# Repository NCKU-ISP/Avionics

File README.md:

# 國立成功大學 太空推進研究社
National Cheng Kung University Institute of Space Propulsion (NCKU ISP)

## Hardwares
### Stable
- ISP555
- ISP8266

### Beta
- ISP32

## Contributing
Contributions are what make the open source community such an amazing place to learn, inspire, and create. Any contributions you make are greatly appreciated.

If you have a suggestion that would make this better, please fork the repo and create a pull request. You can also simply open an issue with the tag "enhancement". Don't forget to give the project a star! Thanks again!

1. Fork the Project
2. Create your Feature Branch (git checkout -b feature/AmazingFeature)
3. Commit your Changes (git commit -m 'Add some AmazingFeature')
4. Push to the Branch (git push origin feature/AmazingFeature)
5. Open a Pull Request

## Contact
If you are interested in our project and want to support us, please contact us with the following:
- aerogroup2020@gmail.com
- [Facebook](https://www.facebook.com/ispncku)

## [LICENSE](https://github.com/NCKU-ISP/Avionics/blob/boards/LICENSE)
Distributed under the BSD 3-clause License. See LICENSE for more information.

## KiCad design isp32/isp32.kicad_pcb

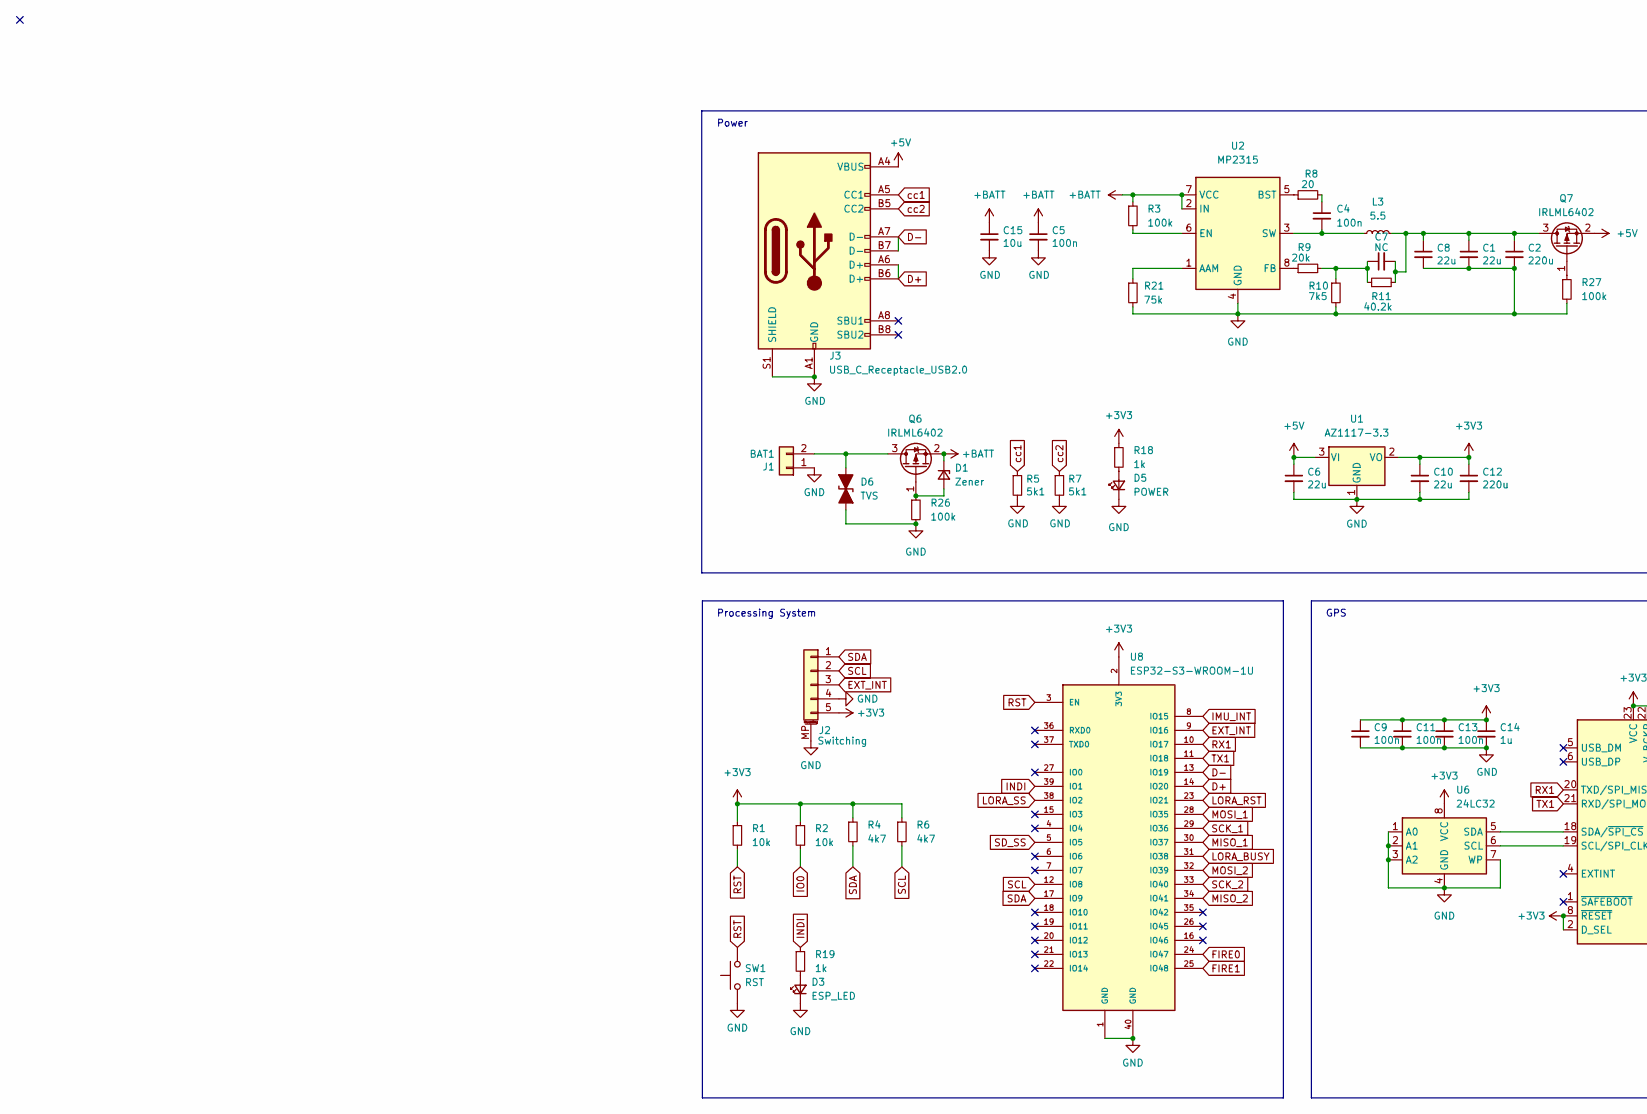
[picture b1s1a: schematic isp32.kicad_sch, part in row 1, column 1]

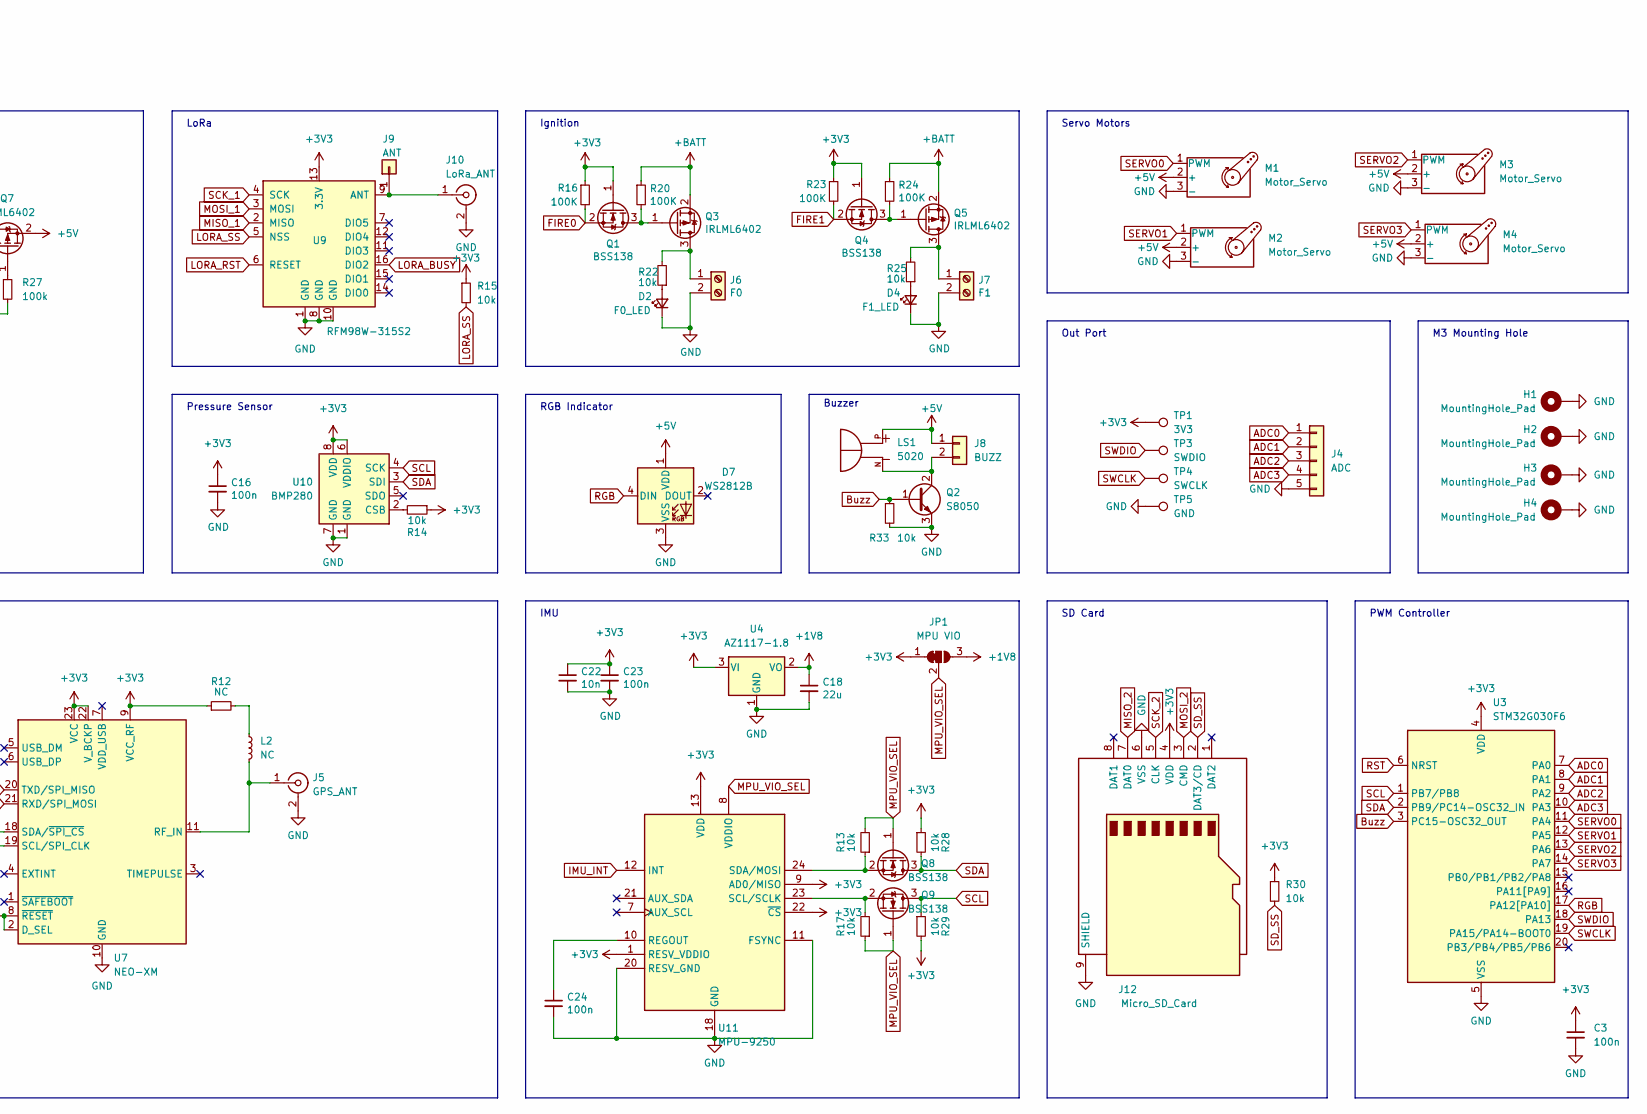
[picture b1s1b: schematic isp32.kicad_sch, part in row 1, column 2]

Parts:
C1, C6, C8, C10, C18: 22u; C_0603_1608Metric
C2, C12: 220u; CP_EIA-3528-12_Kemet-T
C3, C4, C9, C11, C13, C16, C23, C24: 100n; C_0603_1608Metric
C5: 100n; C_0805_2012Metric
C7: NC; C_0603_1608Metric
C14: 1u; C_0603_1608Metric
C15: 10u; C_0805_2012Metric
C22: 10n; C_0603_1608Metric
D1: Zener; D_SOD-123
D2: F0_LED; LED_0603_1608Metric
D3: ESP_LED; LED_0603_1608Metric
D4: F1_LED; LED_0603_1608Metric
D5: POWER; LED_0603_1608Metric
D6: TVS; D_SMB
D7: WS2812B; LED_WS2812B_PLCC4_5.0x5.0mm_P3.2mm
H1, H2, H3, H4: MountingHole_Pad; MountingHole_3.2mm_M3_ISO7380_Pad
J1: BAT1; AMASS_XT60-M_1x02_P7.20mm_Vertical
J2: Switching; Molex_PicoBlade_53261-0571_1x05-1MP_P1.25mm_Horizontal
J3: USB_C_Receptacle_USB2.0; USB_C_Receptacle_Palconn_UTC16-G
J4: ADC; PinHeader_1x05_P1.27mm_Vertical
J5: GPS_ANT; U.FL_Hirose_U.FL-R-SMT-1_Vertical
J6: F0; TerminalBlock_Phoenix_MPT-0,5-2-2.54_1x02_P2.54mm_Horizontal
J7: F1; TerminalBlock_Phoenix_MPT-0,5-2-2.54_1x02_P2.54mm_Horizontal
J8: BUZZ; PinHeader_1x02_P1.27mm_Vertical
J9: ANT; PinHeader_1x01_P2.00mm_Vertical
J10: LoRa_ANT; U.FL_Hirose_U.FL-R-SMT-1_Vertical
J12: Micro_SD_Card; microSD_HC_Molex_47219-2001
JP1: MPU VIO
L2: NC; L_0805_2012Metric
L3: 5.5; L_Sunlord_SWPA5020S
LS1: 5020; XDCR_KSSG33J12-3; PARTREV 1.4
M1, M2, M3, M4: Motor_Servo; PinHeader_1x03_P2.54mm_Vertical
Q1, Q4, Q8, Q9: BSS138; SOT-23
Q2: S8050; SOT-23
Q3, Q5, Q6, Q7: IRLML6402; SOT-23
R1, R2, R13, R14, R15, R17, R22, R25, R28, R29, R30, R33: 10k; R_0603_1608Metric
R3, R26, R27: 100k; R_0603_1608Metric
R4, R6: 4k7; R_0603_1608Metric
R5, R7: 5k1; R_0603_1608Metric
R8: 20; R_0603_1608Metric
R9: 20k; R_0603_1608Metric
R10: 7k5; R_0603_1608Metric
R11: 40.2k; R_0603_1608Metric
R12: NC; R_0603_1608Metric
R16, R20, R23, R24: 100K; R_0603_1608Metric
R18, R19: 1k; R_0603_1608Metric
R21: 75k; R_0603_1608Metric
SW1: RST; SW_SPST_FSMSM
TP1: 3V3; TestPoint_Pad_D1.0mm
TP3: SWDIO; TestPoint_Pad_D1.0mm
TP4: SWCLK; TestPoint_Pad_D1.0mm
TP5: GND; TestPoint_Pad_D1.0mm
U1: AZ1117-3.3; SOT-89-3
U2: MP2315; TSOT-23-8
U3: STM32G030F6; TSSOP-20_4.4x6.5mm_P0.65mm
U4: AZ1117-1.8; SOT-89-3
U6: 24LC32; SOIC-8_3.9x4.9mm_P1.27mm
U7: NEO-XM; ublox_NEO
U8: ESP32-S3-WROOM-1U; XCVR_ESP32-S3-WROOM-1U; PARTREV v0.6
U9: RFM98W-315S2; HOPERF_RFM9XW_SMD
U10: BMP280; Bosch_LGA-8_2x2.5mm_P0.65mm_ClockwisePinNumbering
U11: MPU-9250; InvenSense_QFN-24_3x3mm_P0.4mm

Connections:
+1V8: C18.1, JP1.3 (B), U4.2 (VO)
+3V3: C3.1, C9.1, C10.1, C11.1, C12.1, C13.1, C14.1, C16.1, C22.1, C23.1, J2.5, J12.4 (VDD), JP1.1 (A), Q1.1 (G), Q4.1 (G), R1.1, R2.1, R4.1, R6.1, R12.1, R14.1, R15.1, R16.1, R18.1, R23.1, R28.1, R29.2, R30.1, TP1.1, U1.2 (VO), U3.4 (VDD), U4.3 (VI), U6.8 (VCC), U7.2 (D_SEL), U7.8 (~RESET), U7.9 (VCC_RF), U7.22 (V_BCKP), U7.23 (VCC), U8.2 (3V3), U9.13 (3.3V), U10.6 (VDDIO), U10.8 (VDD), U11.1 (RESV_VDDIO), U11.9 (AD0/MISO), U11.13 (VDD), U11.22 (~CS)
+5V: C6.1, D7.1 (VDD), J3.A4 (VBUS), J3.A9 (VBUS), J3.B4 (VBUS), J3.B9 (VBUS), J8.1, LS1.P, M1.2 (+), M2.2 (+), M3.2 (+), M4.2 (+), Q7.2 (S), U1.3 (VI); also elsewhere on the board
+BATT: C5.1, C15.1, D1.1 (K), Q3.2 (S), Q5.2 (S), Q6.2 (S), R3.1, R20.1, R24.1, U2.2 (IN), U2.7 (VCC); also elsewhere on the board
ADC0: J4.1, U3.7 (PA0)
ADC1: J4.2, U3.8 (PA1)
ADC2: J4.3, U3.9 (PA2)
ADC3: J4.4, U3.10 (PA3)
Buzz: Q2.1 (B), R33.1, U3.3 (PC15-OSC32_OUT)
D+: J3.A6 (D+), J3.B6 (D+), U8.14 (IO20)
D-: J3.A7 (D-), J3.B7 (D-), U8.13 (IO19)
EXT_INT: J2.3, U8.9 (IO16)
FIRE0: Q1.2 (S), R16.2, U8.24 (IO47)
FIRE1: Q4.2 (S), R23.2, U8.25 (IO48)
GND: C1.2, C2.2, C3.2, C5.2, C6.2, C8.2, C9.2, C10.2, C11.2, C12.2, C13.2, C14.2, C15.2, C16.2, C18.2, C22.2, C23.2, C24.2, D2.1 (K), D3.1 (K), D4.1 (K), D5.1 (K), D6.1 (A1), D7.3 (VSS), H1.1, H2.1, H3.1, H4.1, J1.1, J2.4, J2.MP (MountPin), J3.A1 (GND), J3.A12 (GND), J3.B1 (GND), J3.B12 (GND), J3.S1 (SHIELD), J4.5, J5.2 (Ext), J6.2, J7.2, J10.2 (Ext), J12.6 (VSS), J12.9 (SHIELD), M1.3 (-), M2.3 (-), M3.3 (-), M4.3 (-), Q2.3 (E), R5.2, R7.2, R10.2, R21.2, R26.2, R27.2, R33.2, SW1.1, TP5.1, U1.1 (GND), U2.4 (GND), U3.5 (VSS), U4.1 (GND), U6.1 (A0), U6.2 (A1), U6.3 (A2), U6.4 (GND), U6.7 (WP), U7.10 (GND), U7.12 (GND), U7.13 (GND), U7.24 (GND), U8.1 (GND), U8.40 (GND), U8.41_1 (GND), U8.41_2 (GND), U8.41_3 (GND), U8.41_4 (GND), U8.41_5 (GND), U8.41_6 (GND), U8.41_7 (GND), U8.41_8 (GND), U8.41_9 (GND), U9.1 (GND), U9.8 (GND), U9.10 (GND), U10.1 (GND), U10.7 (GND), U11.11 (FSYNC), U11.18 (GND), U11.20 (RESV_GND); also elsewhere on the board
IMU_INT: U8.8 (IO15), U11.12 (INT)
INDI: R19.1, U8.39 (IO1)
IO0: R2.2, U8.27 (IO0)
LORA_BUSY: U8.31 (IO38), U9.16 (DIO2)
LORA_RST: U8.23 (IO21), U9.6 (RESET)
LORA_SS: R15.2, U8.38 (IO2), U9.5 (NSS)
MISO_1: U8.30 (IO37), U9.2 (MISO)
MISO_2: J12.7 (DAT0), U8.34 (IO41)
MOSI_1: U8.28 (IO35), U9.3 (MOSI)
MOSI_2: J12.3 (CMD), U8.32 (IO39)
MPU_VIO_SEL: JP1.2 (C), Q8.1 (G), Q9.1 (G), R13.2, R17.1, U11.8 (VDDIO)
unnamed 26: C1.1, C2.1, C7.2, C8.1, L3.2, Q7.3 (D), R11.2; also elsewhere on the board
unnamed: C4.1, R8.2
unnamed: C4.2, L3.1, U2.3 (SW)
unnamed: C7.1, R9.2, R10.1, R11.1
unnamed: C24.1, U11.10 (REGOUT)
unnamed: D1.2 (A), Q6.1 (G), R26.1
unnamed: D2.2 (A), R22.1
unnamed: D3.2 (A), R19.2
unnamed: D4.2 (A), R25.1
unnamed: D5.2 (A), R18.2
unnamed: D6.2 (A2), J1.2, Q6.3 (D)
unnamed: J5.1 (In), L2.2, U7.11 (RF_IN)
unnamed: J6.1, Q3.3 (D), R22.2
unnamed: J7.1, Q5.3 (D), R25.2
unnamed: J8.2, LS1.N, Q2.2 (C)
unnamed: J9.1, J10.1 (In), U9.9 (ANT)
unnamed: L2.1, R12.2
unnamed: Q1.3 (D), Q3.1 (G), R20.2
unnamed: Q4.3 (D), Q5.1 (G), R24.2
unnamed: Q7.1 (G), R27.1
unnamed: Q8.2 (S), R13.1, U11.24 (SDA/MOSI)
unnamed: Q9.2 (S), R17.2, U11.23 (SCL/SCLK)
unnamed: R3.2, U2.6 (EN)
unnamed: R8.1, U2.5 (BST)
unnamed: R9.1, U2.8 (FB)
unnamed: R14.2, U10.2 (CSB)
unnamed: R21.1, U2.1 (AAM)
unnamed: U6.5 (SDA), U7.18 (SDA/~SPI_CS)
unnamed: U6.6 (SCL), U7.19 (SCL/SPI_CLK)
RGB: D7.4 (DIN), U3.17 (PA12[PA10])
RST: R1.2, SW1.2, U3.6 (NRST), U8.3 (EN)
RX1: U7.20 (TXD/SPI_MISO), U8.10 (IO17)
SCK_1: U8.29 (IO36), U9.4 (SCK)
SCK_2: J12.5 (CLK), U8.33 (IO40)
SCL: J2.2, Q9.3 (D), R6.2, R29.1, U3.1 (PB7/PB8), U8.12 (IO8), U10.4 (SCK)
SDA: J2.1, Q8.3 (D), R4.2, R28.2, U3.2 (PB9/PC14-OSC32_IN), U8.17 (IO9), U10.3 (SDI)
SD_SS: J12.2 (DAT3/CD), R30.2, U8.5 (IO5)
SERVO0: M1.1 (PWM), U3.11 (PA4)
SERVO1: M2.1 (PWM), U3.12 (PA5)
SERVO2: M3.1 (PWM), U3.13 (PA6)
SERVO3: M4.1 (PWM), U3.14 (PA7)
SWCLK: TP4.1, U3.19 (PA15/PA14-BOOT0)
SWDIO: TP3.1, U3.18 (PA13)
TX1: U7.21 (RXD/SPI_MOSI), U8.11 (IO18)
cc1: J3.A5 (CC1), R5.1
cc2: J3.B5 (CC2), R7.1

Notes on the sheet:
IMU
PWM Controller
Ignition
M3 Mounting Hole
Servo Motors
RGB Indicator
Out Port
Buzzer
Processing System
Pressure Sensor
LoRa
GPS
SD Card
Power

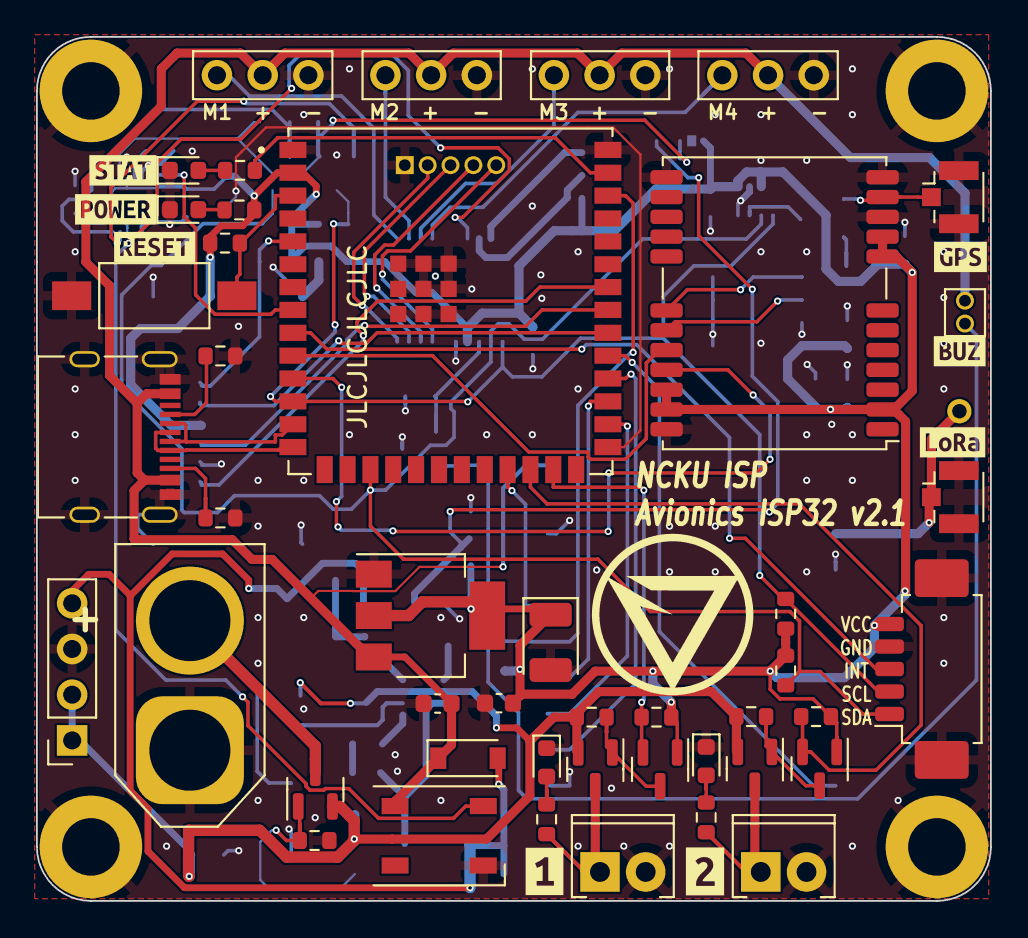
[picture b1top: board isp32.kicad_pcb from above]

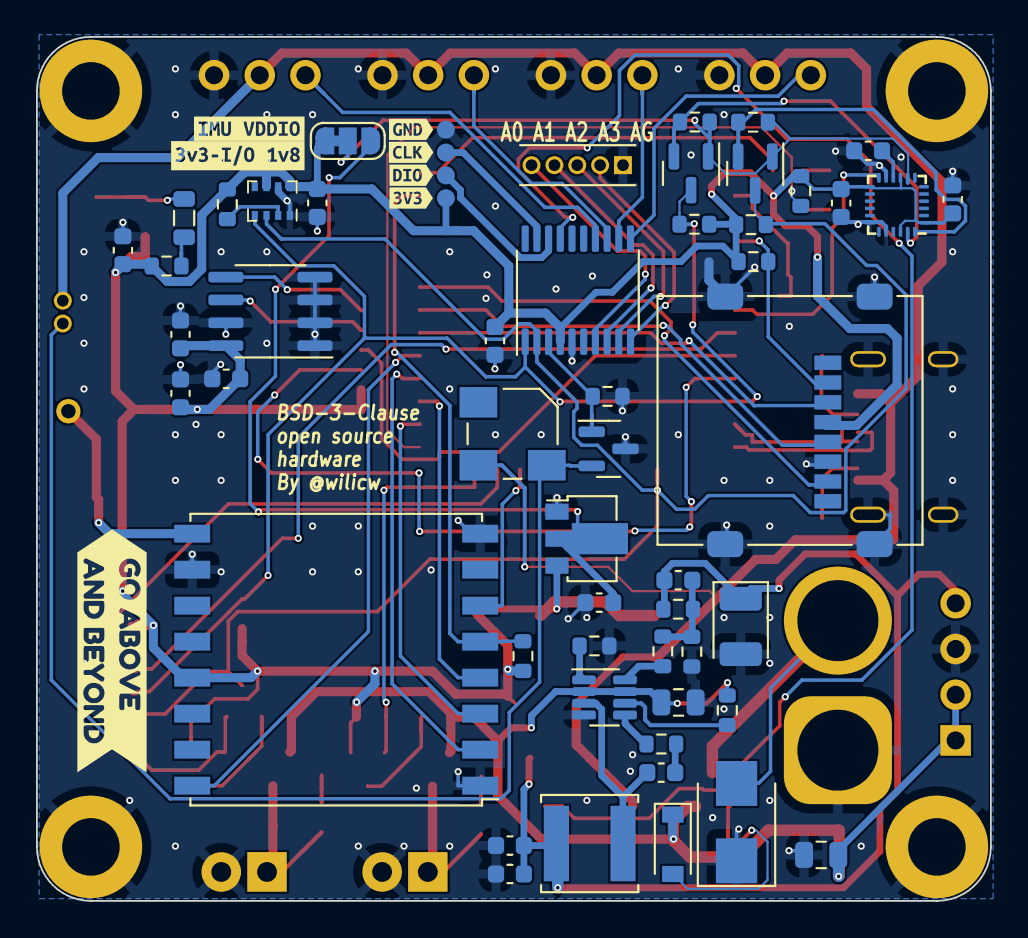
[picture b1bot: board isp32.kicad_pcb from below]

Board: 2 copper layers, 53.0 x 48.0 mm, 120 parts (62 on the bottom side), 71 nets.

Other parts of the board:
D8: D_Shockley; D_SOD-123
J11: Power Modules; PinSocket_1x04_P2.54mm_Vertical
kibuzzard-63CD1E7F: G***; kibuzzard-63CD1E7F
kibuzzard-63CD1E61: G***; kibuzzard-63CD1E61
kibuzzard-63CD1EC0: G***; kibuzzard-63CD1EC0
kibuzzard-63CD1EC5: G***; kibuzzard-63CD1EC5
kibuzzard-63CD04EB: G***; kibuzzard-63CD04EB
kibuzzard-63CD04FB: G***; kibuzzard-63CD04FB
kibuzzard-641A73AC: G***; kibuzzard-641A73AC
kibuzzard-641A73E5: G***; kibuzzard-641A73E5
kibuzzard-641A73FA: G***; kibuzzard-641A73FA
kibuzzard-641A737F: G***; kibuzzard-641A737F
kibuzzard-641A7395: G***; kibuzzard-641A7395
kibuzzard-641A7704: G***; kibuzzard-641A7704
kibuzzard-642D96EE: G***; kibuzzard-642D96EE
kibuzzard-642D96F8: G***; kibuzzard-642D96F8
kibuzzard-642D97EE: G***; kibuzzard-642D97EE

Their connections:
+5V: D8.1 (K); also elsewhere on the board
+BATT: J11.1, J11.2; also elsewhere on the board
GND: J11.3; also elsewhere on the board
unnamed 26: D8.2 (A), J11.4; also elsewhere on the board

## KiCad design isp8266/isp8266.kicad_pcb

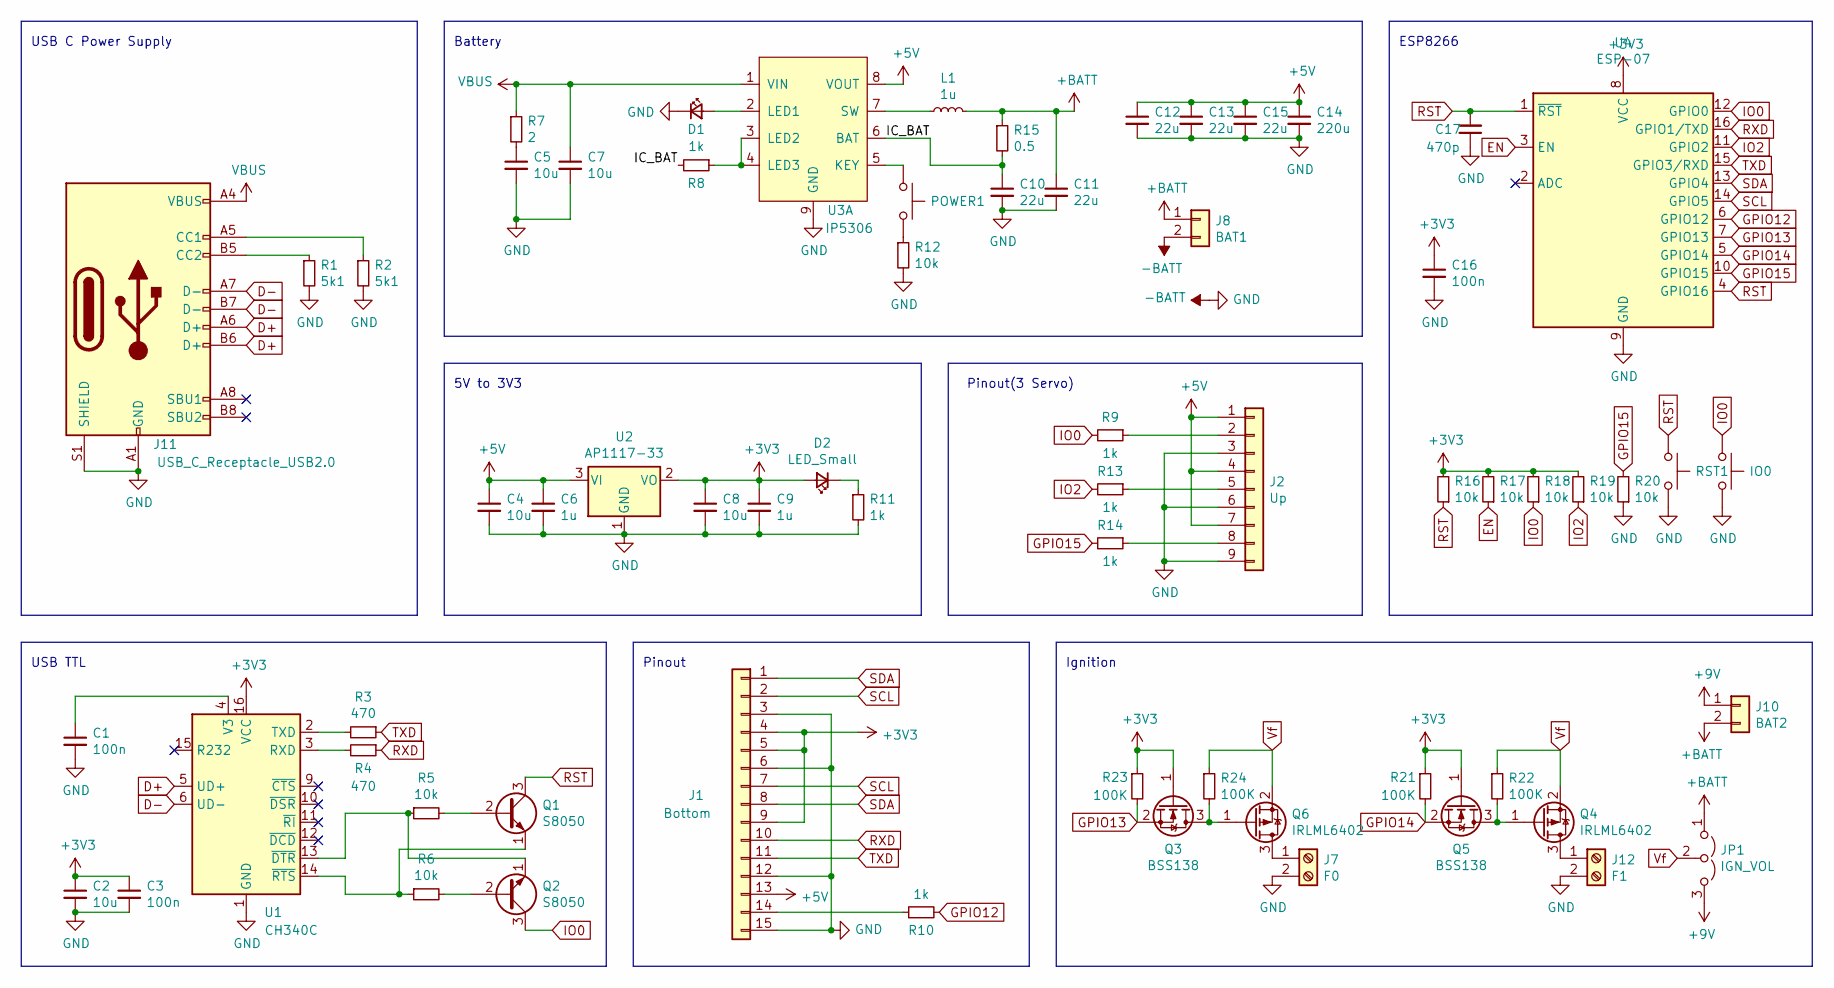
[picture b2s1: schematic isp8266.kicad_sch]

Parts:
C1, C3, C16: 100n; C_0603_1608Metric
C2, C4, C5, C7, C8: 10u; C_0603_1608Metric
C6, C9: 1u; C_0603_1608Metric
C10, C11, C12, C13, C15: 22u; C_0603_1608Metric
C14: 220u; CP_EIA-3528-12_Kemet-T
C17: 470p; C_0603_1608Metric
D1, D2: LED_Small; LED_0603_1608Metric
IO0: SW_Push; SW_SPST_B3U-1000P
J1: Bottom; PinHeader_1x15_P2.54mm_Vertical
J2: Up; PinHeader_1x09_P2.54mm_Vertical
J7: F0; TerminalBlock_Phoenix_MPT-0,5-2-2.54_1x02_P2.54mm_Horizontal
J8: BAT1; JST_XH_B2B-XH-A_1x02_P2.50mm_Vertical
J10: BAT2; JST_XH_B2B-XH-A_1x02_P2.50mm_Vertical
J11: USB_C_Receptacle_USB2.0; USB_C_Receptacle_Palconn_UTC16-G
J12: F1; TerminalBlock_Phoenix_MPT-0,5-2-2.54_1x02_P2.54mm_Horizontal
JP1: IGN_VOL; PinHeader_1x03_P2.54mm_Vertical
L1: 1u; L_Abracon_ASPI-0630LR
POWER1: SW_Push; SW_SPST_EVQPE1
Q1, Q2: S8050; SOT-23
Q3, Q5: BSS138; SOT-23
Q4, Q6: IRLML6402; SOT-23
R1, R2: 5k1; R_0603_1608Metric
R3, R4: 470; R_0603_1608Metric
R5, R6, R12, R16, R17, R18, R19, R20: 10k; R_0603_1608Metric
R7: 2; R_0603_1608Metric
R8, R9, R10, R11, R13, R14: 1k; R_0603_1608Metric
R15: 0.5; R_0603_1608Metric
R21, R22, R23, R24: 100K; R_0603_1608Metric
RST1: SW_Push; SW_SPST_EVQPE1
U1: CH340C; SOIC-16_3.9x9.9mm_P1.27mm
U2: AP1117-33; SOT-223-3_TabPin2
U3: IP5306; HTSOP-8-1EP_3.9x4.9mm_P1.27mm_EP2.4x3.2mm
U4: ESP-07

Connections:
+3V3: C2.1, C3.1, C8.1, C9.1, C16.1, D2.2 (A), J1.4, J1.5, J1.9, Q3.1 (G), Q5.1 (G), R16.2, R17.2, R18.2, R19.2, R21.1, R23.1, U1.16 (VCC), U2.2 (VO), U4.8 (VCC)
+5V: C4.1, C6.1, C12.1, C13.1, C14.1, C15.1, J1.13, J2.1, J2.4, J2.7, U2.3 (VI), U3.8 (VOUT)
+9V: J10.1, JP1.3 (B)
+BATT: C11.1, J8.1, J10.2, JP1.1 (A), L1.2, R15.1
-BATT: C1.2, C2.2, C3.2, C4.2, C5.2, C6.2, C7.2, C8.2, C9.2, C10.2, C11.2, C12.2, C13.2, C14.2, C15.2, C16.2, C17.1, D1.1 (K), IO0.2, J1.3, J1.6, J1.12, J1.15, J2.3, J2.6, J2.9, J7.2, J8.2, J11.A1 (GND), J11.A12 (GND), J11.B1 (GND), J11.B12 (GND), J11.S1 (SHIELD), J12.2, R1.2, R2.2, R11.2, R12.2, R20.1, RST1.2, U1.1 (GND), U2.1 (GND), U3.9 (GND), U4.9 (GND)
/IC_BAT: C10.1, R8.2, R15.2, U3.6 (BAT)
D+: J11.A6 (D+), J11.B6 (D+), U1.5 (UD+)
D-: J11.A7 (D-), J11.B7 (D-), U1.6 (UD-)
EN: R17.1, U4.3 (EN)
GPIO12: R10.2, U4.6 (GPIO12)
GPIO13: Q3.2 (S), R23.2, U4.7 (GPIO13)
GPIO14: Q5.2 (S), R21.2, U4.5 (GPIO14)
GPIO15: R14.2, R20.2, U4.10 (GPIO15)
IO0: IO0.1, Q2.3 (C), R9.2, R18.1, U4.12 (GPIO0)
IO2: R13.2, R19.1, U4.11 (GPIO2)
unnamed: C1.1, U1.4 (V3)
unnamed: C5.1, R7.2
unnamed: D1.2 (A), U3.2 (LED1)
unnamed: D2.1 (K), R11.1
unnamed: J1.14, R10.1
unnamed: J2.2, R9.1
unnamed: J2.5, R13.1
unnamed: J2.8, R14.1
unnamed: J7.1, Q6.3 (D)
unnamed: J11.A5 (CC1), R2.1
unnamed: J11.B5 (CC2), R1.1
unnamed: J12.1, Q4.3 (D)
unnamed: L1.1, U3.7 (SW)
unnamed: POWER1.1, U3.5 (KEY)
unnamed: POWER1.2, R12.1
unnamed: Q1.1 (E), R6.1, U1.14 (~RTS)
unnamed: Q1.2 (B), R5.2
unnamed: Q2.1 (E), R5.1, U1.13 (~DTR)
unnamed: Q2.2 (B), R6.2
unnamed: Q3.3 (D), Q6.1 (G), R24.2
unnamed: Q4.1 (G), Q5.3 (D), R22.2
unnamed: R3.2, U1.2 (TXD)
unnamed: R4.2, U1.3 (RXD)
unnamed: R8.1, U3.3 (LED2), U3.4 (LED3)
RST: C17.2, Q1.3 (C), R16.1, RST1.1, U4.1 (~RST), U4.4 (GPIO16)
RXD: J1.10, R4.1, U4.16 (GPIO1/TXD)
SCL: J1.2, J1.7, U4.14 (GPIO5)
SDA: J1.1, J1.8, U4.13 (GPIO4)
TXD: J1.11, R3.1, U4.15 (GPIO3/RXD)
VBUS: C7.1, J11.A4 (VBUS), J11.A9 (VBUS), J11.B4 (VBUS), J11.B9 (VBUS), R7.1, U3.1 (VIN)
Vf: JP1.2 (C), Q4.2 (S), Q6.2 (S), R22.1, R24.1

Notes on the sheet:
USB TTL
ESP8266
Ignition
Pinout(3 Servo)
Battery
Pinout
USB C Power Supply
5V to 3V3

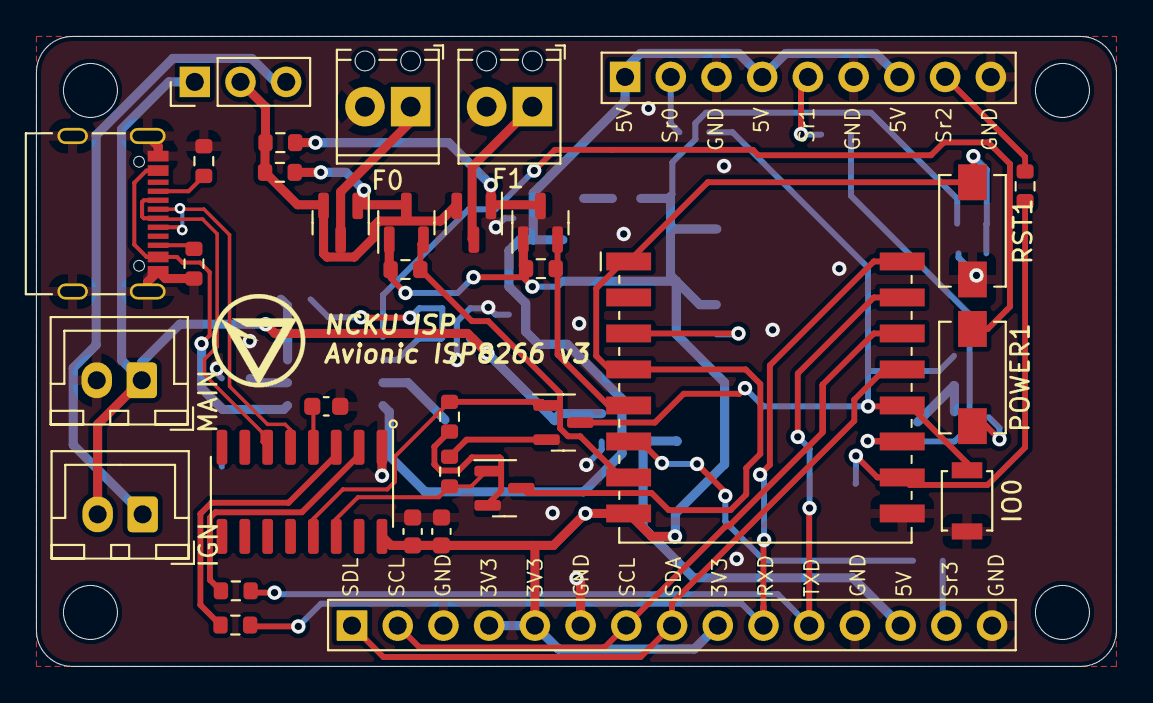
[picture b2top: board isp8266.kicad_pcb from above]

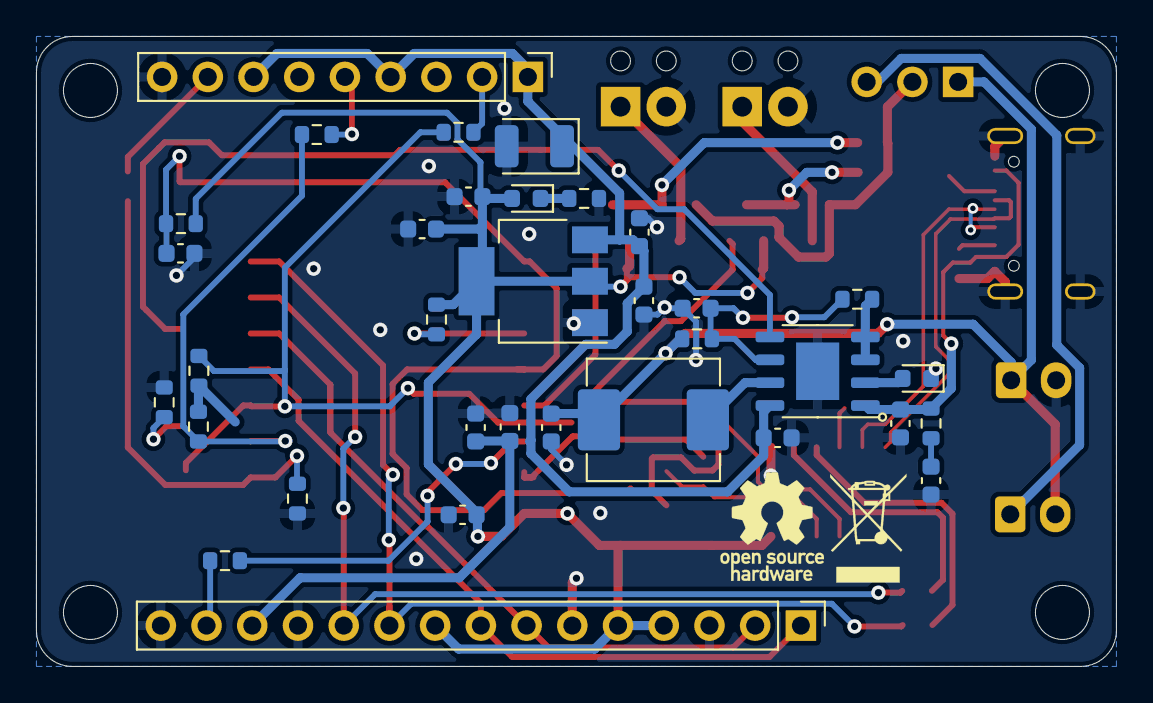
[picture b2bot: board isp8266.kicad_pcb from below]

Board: 2 copper layers, 60.0 x 35.0 mm, 65 parts (34 on the bottom side), 46 nets.

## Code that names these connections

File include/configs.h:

#ifndef _CONFIG_H
#define _CONFIG_H

#include "Arduino.h"


/*--------------- BOARD_VERSIOIN_SETTING ---------------*/
// #define V1_ATMEGA328P
#define V2_ESP8266
// #define V2_ESP32
// #define V3_PIONEER

/*--------------- System function enable ---------------*/
#define USE_SERIAL_DEBUGGER
#define USE_SERIAL_COMMS
// #define GROUND_STATION
// #define GROUND_IGNITOR
#define ONBOARD_AVIONICS
#ifdef GROUND_STATION
#ifndef USE_SERIAL_DEBUGGER
#define USE_SERIAL_DEBUGGER
#endif
#ifndef USE_SERIAL_COMMS
#define USE_SERIAL_COMMS
#endif
#elif defined(ONBOARD_AVIONICS)
// #define USE_GPS_NEO6M
#define USE_PERIPHERAL_BMP280
// #define USE_PERIPHERAL_BMP280_LIB
// #define USE_PERIPHERAL_MPU6050
#define USE_GY91_MPU9250
#define USE_PERIPHERAL_BUZZER
#define PARACHUTE_TRIGGER
#define PARACHUTE_TRIGGER_2
#define DE_SPIN_CONTROL
// #define PARACHUTE_SERVO
#elif defined(GROUND_IGNITOR)
#define LAUNCH_TRIGGER
#endif

// #define USE_SERVO_CONTROL
// #define ENGINE_LOADING_TEST

#if defined(V1_ATMEGA328P) || defined(V2_ESP32)
#define USE_PERIPHERAL_SD_CARD
#define USE_LORA_COMMUNICATION
#define USE_DUAL_SYSTEM_WATCHDOG
#elif defined(V2_ESP8266) || defined(V3_PIONEER)
#define USE_WIFI_COMMUNICATION
#define USE_ESPNOW_COMMUNICATION
#define USE_FILE_SYSTEM
#endif

/*--------------------- PIN_SETTING --------------------*/
#ifdef USE_DUAL_SYSTEM_WATCHDOG
#define PIN_PARTNER_RESET 8
#endif

// Communication
// A0~A5 map to 14~19
// A0-14, A1-15, A2-16, A3-17, A4-18, A5-19
#ifdef USE_LORA_COMMUNICATION
#define PIN_LORA_INTERRUPT 3
#define PIN_LORA_BUSY A2
#define PIN_LORA_RESET A3
#define PIN_LORA_SELECT A1

#define RF_FREQUENCY 433000000  // Hz  center frequency
#define TX_OUTPUT_POWER 22      // dBm tx output power
#define LORA_BANDWIDTH \
    4  // bandwidth=125khz  0:250kHZ,1:125kHZ,2:62kHZ,3:20kHZ.... look for radio
// line 392
#define LORA_SPREADING_FACTOR 7  // spreading factor=11 [SF5..SF12]
#define LORA_CODINGRATE \
    1  // [1: 4/5,
       //  2: 4/6,
       //  3: 4/7,
       //  4: 4/8]

#define LORA_PREAMBLE_LENGTH 8            // Same for Tx and Rx
#define LORA_SYMBOL_TIMEOUT 0             // Symbols
#define LORA_FIX_LENGTH_PAYLOAD_ON false  // variable data payload
#define LORA_IQ_INVERSION_ON false
#define LORA_PAYLOADLENGTH \
    0  // 0: variable receive length
       // 1..255 payloadlength
#endif

#ifdef USE_DUAL_SYSTEM_WATCHDOG
#define PIN_SPI_CS_PARTNER 10
#endif

// PIN assignment
#ifdef V1_ATMEGA328P
#define PIN_TRIGGER_1 6
#define PIN_MOTOR 5
#ifdef USE_PERIPHERAL_BUZZER
#define PIN_BUZZER 2
#endif
#elif defined(V2_ESP8266)
#ifdef LAUNCH_TRIGGER
#define PIN_TRIGGER_1 12
#endif
#ifdef PARACHUTE_TRIGGER
#define PIN_TRIGGER_2 14
#elif defined(PARACHUTE_SERVO)
#define PIN_MOTOR 13
#endif
#ifdef PARACHUTE_TRIGGER_2
#define PIN_TRIGGER_1 12
#endif

#ifdef USE_PERIPHERAL_BUZZER
#define BUZ_ON_LEVEL 0  // Buzzer buzz on high or low
#define PIN_BUZZER 3
#endif

#define SERVO_PULSE_MIN 500
#define SERVO_PULSE_MAX 2500
#ifdef USE_SERVO_CONTROL
#define PIN_SERVO_1 0
#define PIN_SERVO_2 2
#define PIN_SERVO_3 13
#define PIN_SERVO_4 15
#endif

#elif defined(V2_ESP32)
#define PIN_TRIGGER_1 6
#define PIN_MOTOR 5
#elif defined(V3_PIONEER)
#define S0 0
#define S1 2
#define S2 15
#define PIN_CD4051 \
    13  // Every IO using CD4051 as output use "_" at the head of its name
#define _PIN_FIRE_0 5
#define _PIN_FIRE_1 7
#define PIN_MOTOR_T0 \
    14  // T0 is using ESP-07s GPIO14, therefore there is no "_" before "PIN"
#define _PIN_MOTOR_T1 \
    0  // T1 is using CD4051 IO0, therefore it use "_" at the head
#define _PIN_MOTOR_M1 1
#define _PIN_MOTOR_M2 2
#define _PIN_MOTOR_M3 3
#define _PIN_MOTOR_M4 4
#define _PIN_MOTOR_M5 6
#define PIN_INDICATOR 2
#ifdef USE_PERIPHERAL_BUZZER
#define PIN_BUZZER 0
#endif
#endif

/*------------------ WIFI Communication ------------------*/
#define AP_AS_SERVER  // Access point as server (Sky)
// #define STA_AS_SERVER  // Station as server (Ground)
#ifdef V2_ESP8266
#define WIFI_SSID "isp8266_fire"  // default ssid
#define WIFI_PASSWARD NULL        //"ESP8266_avionics"  // default passward
#define WIFI_HOST_NAME "nckuisp"  // default host name
#elif defined(V3_PIONEER)
#define WIFI_SSID "Pioneer"       // default ssid
#define WIFI_PASSWARD "Pioneer1"  // default passward
#define WIFI_HOST_NAME "nckuisp"  // default host name
#endif


/*------------ Configuration for parachute --------------*/
#define V3_1
#ifdef V3_1
#define SERVO_CLOSED_ANGLE 110
#define SERVO_RELEASE_ANGLE 170
#elif defined(V3_2)
#define SERVO_CLOSED_ANGLE 80
#define SERVO_RELEASE_ANGLE 150
#endif
#define release_by_time
#ifdef PARACHUTE_TRIGGER_2
#define CHUTE_DELAY_TIME 1000
#endif
#define RELEASE_TIME 12000
#define STOP_TIME 55000
#define PID_ON_TIME 4000

/*------------------ Constants for imu ------------------*/
#ifdef USE_PERIPHERAL_MPU6050
// #define USE_MPU_ISP_INTERFACE
//  IMU interrupt
//  Only available on specific pins,
//  328: 2, 3,
//  32u4: 0, 1, 22, 3, 7
#define PIN_IMU_INT 2
// an MPU9250 object with the MPU-9250 sensor on I2C bus 0 with address 0x68
#define IMU_MPU_ADDR 0x68


#ifdef USE_MPU_ISP_INTERFACE
#define PIN_SPI_CS_IMU 9
#endif
#endif

// BMP280 setting
#ifdef USE_PERIPHERAL_BMP280
// #define IMU_BMP_ADDR       0x76
//  The sampling times of sea level pressure while initializing
#define IMU_BMP_SEA_LEVEL_PRESSURE_SAMPLING 50
#define IMU_BMP_SAMPLING_PERIOD 8  // ms
#endif
// Altitude setting
// tau = (-T) / log(a), with a=0.8 and T=10(ms), tau about to 103.2 (ms)
#define IMU_ALTITUDE_SMOOTHING_CONSTANT 0.0f
#define IMU_RISING_CRITERIA 1.0f
#define IMU_FALLING_CRITERIA -0.8f

/*---------------------- Data logger --------------------*/
#ifdef USE_PERIPHERAL_SD_CARD
#define LOGGER_SD_CS 10
#define LOGGER_FILENAME_BUFFER 20
#elif defined(USE_FILE_SYSTEM)
//
// Choose using SPIFF or LittleFS as filesystem engine.
// You can only choose one of these
// If you don't comment one of them. LittleFS would be chosed
//
#define LITTLE_FS  // default
// #define SPIFF
#endif
#define LOGGER_FILENAME "logger"
#define LOGGER_FILE_EXT ".txt"
#define LOGGER_LOG_INTERVAL 100

/*-------------------- Serial debugger ------------------*/
#ifdef USE_SERIAL_DEBUGGER
#define SERIAL_DEBUGGER_BAUDRATE 115200
#elif defined(USE_SERIAL_COMMS)
#define SERIAL_COMMS_BAUDRATE 9600
#ifdef ESP8266
#define PIN_GPS_RX 3
#define PIN_GPS_TX 1
#endif
#endif

/*------------------ Watchdog protection ----------------*/
#ifdef USE_DUAL_SYSTEM_WATCHDOG
#define WATCH_SPI_TIMEOUT 100  // ms
#endif

enum ERROR_CODE {
    ERROR_OK,
    ERROR_SD_INIT_FAILED,
    ERROR_MPU_INIT_FAILED,
    ERROR_DMP_INIT_FAILED,
    ERROR_BMP_INIT_FAILED,
    ERROR_IMU_INIT_FAILED
};

enum INFO_CODE {
    INFO_LOGGER_INIT,
    INFO_IMU_INIT,
    INFO_SERVO_INIT,
    INFO_ALL_SYSTEM_INIT,
    INFO_LORA_INIT
};

#define LIFT_OFF_PROTECT_TIME 1000
#define IMU_LIFT_OFF_DETECTION_G 2.5f

#endif

#ifdef ENGINE_LOADING_TEST
#define DT_PIN 2
#define SCK_PIN 0
#define SCALE_FACTOR 110
#define LOADCELL_SAMPLING_RATE 80  //(hz)
#endif

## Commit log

2020-10-25 Initial commit Add avionics source code, with Wire.h problem remain. Sensor fusion algorithm in lack.
2020-12-28 Modulize the avionic system - Using Adafruit_BMP280 library to handle BMP280 - Using configs.h to activate modules
2021-01-05 Use clang-format to standardize format
    add `.clang-format` setting, so someone can use clang-format -i file
    to automatically adjust the cpp file format.
2021-01-05 Add new buzzer mode
    Use an enum to indicate a buzzering type, one can choose or create
    their new mode with simply adding the enum and the buzzer() function
    in `core.cpp`.
2021-01-05 Fix bugs in bmp280 initialization and data reading
    - There is a bug that a system object can't initailize in global scope,
    so I moved it into the setup() function.
    - Add ROCKET_POSE in imu class so as to indicate some simple pose state,
    including unknown, rising, falling, etc.
2021-01-05 Add servo features
    Add a function called `parachute()` to perform the task of release
    the parachute, and one can use an electronic ignition or a pwm
    controlled servo motor to trigger the mechanic motion.
2021-01-05 Continuous logging with a constant interval
    Log data in a constant interval to save IO usage time but with
    continuous rocket pose judgement.
2021-01-11 Fix bugs in servo driven parachute release
    Because that the function Servo::read() returns the value of previous
    written command in Servo::write(), the original design of while loop
    is not pratical. Therefore, I remove that and add a new function
    System::parachute_release() to allow the programmer to release the
    servo manually.
2021-01-11 pcb files initial commit
    The pcb designed with altium 19.04.
2021-01-17 Fixed bugs of the first pcb layout generation
    - Fix power stability
    - Put buzzor directly on board
    - Use new type ignitor connector
    - Add parachute indicating LED
2021-03-05 Replace mpu6050 module to enable the DMP
    Use this library, jrowberg/i2cdevlib, https://github.com/jrowberg/i2cdevlib,
    to enable the DMP on the MPU6050. To avoid the error on including
    multiple times in the source code, I seperated the definition and
    the declaration of the MPU6050_6Axis_MotionApps20.
2021-03-06 Add Lora feature
    Use SX126x.h library to handle the lora module, uncomment the line
    'USE_LORA_COMMUNICATION' to enable the features.
2021-03-06 Code minimization
    Trying to minimize the program usage:
    1. Avoid the using of const string.
    2. Use preprocessor to modulize the buzzer feature.
    3. Use error code and info code to represent errors and information.
2021-03-06 Simplify log functions
    Combine log_error() and log_info() into log_code(). As one wants to log
    code-like messages, one needs to specify the error type.
2021-03-06 Add simplified BMP280 library
    Import library from AdafruitBMP280 library to minimize the program
    size.
2021-04-13 Create LICENSE
2021-05-14 Add new version avionics program
    The new version of our avionic system was developed by platformIO, and
    use esp32 as the controller.
2021-06-26 Add new Lora module based on SX1267
    Bump with new lora library which is based on esp32 freeRTOS system.
    It handles the Lora module communication better and it has been tested
    on esp32 multithread applications successfully. This module applied a
    callback machanism and equipped with dual rx/tx packet queue, providing
    a more stable communication.
    The new style packet use a LoraPacket class as a middle data type
2021-06-26 Add GPS module based on Neo 6m
    Bump with NMEAGPS library, and add a new module to record data from
    Gps.
2021-07-16 Use semaphore to protect the SPI bus
    After applying multitasking, the racing condition on SPI bus caused
    the SD card and LORA conflicting with each other. The semaphore
    restrict the manipulation of the SPI to avoid this.
2021-07-16 Add ground station
2022-03-17 Create the isp_8266 project
2022-03-17 Fix .gitignore and plant the former code in.
2022-03-23 Make the code more neat.
2022-03-27 Prepare to launch for Yengchen III.
2022-05-28 Close fairing at booting.
2022-10-07 Saving files before refreshing line endings
2022-10-07 Normalize all the line endings
2022-10-25 Re-organize project files and libraries
2022-10-28 Create git hook
2022-11-01 Fix ESPNOW multiple definitions
2022-11-01 Lower the upload speed
2022-11-01 Fix return statement
2022-11-01 Enable ESPNOW
2022-11-08 fix: restricted serial.read() character's range
2022-11-08 feat: implement ESP NOW communication
2022-11-08 feat: don't disable serial when enable debug
2022-11-08 feat: broadcast command via network
2022-11-09 feat: broadcast esp now message to all peer
2022-11-09 fix: change git commit format and cppcheck paras
2022-11-09 fix: passing const string ref into broadcast func
2022-11-12 feat(esp-now): implement command fetch in core
2022-11-12 fix: githooks format command
2022-11-12 fix: core string concat error
2022-11-14 Complete esp now send/recv features
2022-11-27 Initial commit on orphan branch
2022-11-27 Create isp8266 kicad project
2022-11-27 Modify some components' position
2022-11-27 Move folder and create IPS5306 lib
2022-11-27 Add ignore file for kicad project
2022-11-27 Annotate all symbols
2022-11-27 Add rst button and footprint
2022-11-27 Use USB_C_Receptacle
2022-11-27 Complete power sch
2022-11-27 Complete all peripherals
2022-11-27 Typo
2022-11-27 Add IO0 button
2022-11-27 Schematics PDF
2022-11-27 Change I2C connector
2022-11-27 Change usb c connector
2022-11-27 Modify NMOS and footprint
2022-11-27 Edit BJT footprint
2022-11-27 Change ignition circuits
2022-11-27 Add isp logo footprint
2022-11-27 Modify symbol location
2022-11-27 Mirror IMU pin and update footprint
2022-11-27 Add text and logo
2022-11-27 Text and some routing
2022-11-27 Routing
2022-11-27 Change pinout connector
2022-11-27 Connect battery in series
2022-11-27 Change switch position and battery connector
2022-11-27 Update PDF
2022-11-27 Use kicad and panelized
2022-11-27 Fix silks
2022-11-27 Ignore jlc files
2022-11-28 Use define to seperate avionics and ground station
2022-11-30 fix: add multi-device MAC address
2022-12-02 Calibrate imu and add reaction wheel pid control
2022-12-02 fix: change mac address
2022-12-02 feat: disable websocket and server loop
    Disable websocket and server when esp-now is enabled
2022-12-02 feat: add eeprom cofig loader and format code
2022-12-02 feat: add pid config
2022-12-02 Start up sequence for reaction wheel pid control
2022-12-07 Reset footprint and export 3d file
2023-01-06 Create ISP32 board and complete power block
2023-01-06 ESP32 module
2023-01-09 Complete sensors and servos
2023-01-09 Change GPS to I2C
2023-01-10 Complete isp32 v1 schemtics
2023-01-10 Remove 1.2V LDO
2023-01-10 Add ispICE40 schemtics
2023-01-10 Select isp32 footprint
2023-01-11 Change footprint and layout
2023-01-11 Rough layout
2023-01-11 New schematics pdf
2023-01-11 Split motor and add tp
2023-01-11 Add logo and modify layout
2023-01-12 Fix ESD
2023-01-12 Add M3 mounting hole
2023-01-12 Fix overlap
2023-01-12 Resolve overlap
2023-01-12 Complete routing
2023-01-12 Add vias
2023-01-12 Change LoRa antenna
2023-01-12 Plot new pdf file
2023-01-12 Add silkscreen and logo
2023-01-12 Add 3d models
2023-01-12 Change buzzer type
2023-01-12 Switching port flip
2023-01-13 Add water mark
2023-01-13 Add sd card and pwm controller
2023-01-13 New pcb
2023-01-13 New design with esp32s3
2023-01-16 Change power circuits
2023-01-17 Replace F0 to G0
2023-01-17 Rough route
2023-01-18 panelization
2023-01-22 Change label style
2023-01-26 Change label and panel size
2023-01-29 Update the 3d model file
2023-01-29 Add license and readme
2023-03-22 Fix all isp32 issues
2023-04-05 feat: add level converter to imu
2023-04-05 feat: add pdf
2023-12-19 feat: isp32 2023 12 19
